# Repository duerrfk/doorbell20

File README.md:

# What is DoorBell20?

Door Bell 2.0 (or DoorBell20 for short) is a Bluetooth Low Energy (BLE) appliance to monitor a door bell and send notifications whenever the door bell rings. It turns a conventional door bell into a smart door bell that can be connected to the Internet of Things (IoT). Thus, DoorBell20 is the modern version of a door bell, or, as the name suggests, the door bell version 2.0 for the IoT era.

DoorBell20 consists for two major parts:

* The DoorBell20 monitoring device, which is connected in parallel to the door bell and wirelessly via BLE to a client running on a remote IoT gateway, e.g., a Raspberry Pi with Bluetooth stick.
* A DoorBell20 client running on the IoT gateway passing on notifications received via BLE to a remote cloud service. Different clients can be implemented for different IoT cloud services. So far, DoorBell20 includes a client for [If This Then That (IFTTT)](https://ifttt.com), which makes it very easy to trigger different actions when a door bell event is detected. For instance, a notification can be sent to a mobile phone or trigger an IP camera installed at the door to take pictures.

```
                  [IoT Cloud Service]
                  [  (e.g., IFTTT)  ]
                           | ^
                 Internet  | | Door Bell Event Notifications
                           |
                [      IoT Gateway      ]
                [ w/ DoorBell20 Client  ]
                [ (e.g., IFTTT Trigger) ]
                           |  ^
           BLE Connection  |  | Door Bell Event Notifications  
                           |
|-----------[DoorBell20 Monitoring Device]---------|
|                                                  |
|--------------------[Door Bell]-------------------|
|                                                  |
|                                                  |
|                                                 \   Door Bell Push Button
|                                                  \
|                                                  |
|----------------(Voltage Source)------------------|
                 (    12 VAC    )
```  

The following images show the DoorBell20 monitoring device, its connection to a door bell, and a door bell event notification displayed by the If This Then That (IFTTT) app on a mobile phone. 

The main features of DoorBell20 are:

* Open-source software and hardware. Source code for the door bell monitoring device and IFTTT client as well as Eagle files (schematic and board layout) are provided.
* Maker-friendly: using easily available cheap standard components (nRF51822 BLE chip, standard electronic parts), easy to manufacture circuit board, and open-source software and hardware design.
* Includes a client for the popular and versatile If This Then That (IFTTT) service to facilitate the development of IoT applications integrating DoorBell20. 
* Liberal licensing of software and hardware under the Apache License 2.0 and the CERN Open Hardware License 1.0, respectively.

# DoorBell20 Monitoring Device

## Hardware

The following images show the DoorBell20 hardware and schematic.

The DoorBell20 monitoring device is based on the BLE chip [nRF51822](https://www.nordicsemi.com/eng/Products/Bluetooth-low-energy/nRF51822) by Nordic Semiconductors. The nRF51822 features an ARM Cortex M0 processor implementing both, the application logic and the BLE stack (so-called softdevice). DoorBell20 uses the S110 softdevice version 8.0. See next sub-section on how to flash the softdevice and the application code. We use a so-called "Bluetooth 4.0" breakout boards with an nRF51822 (version 3, variant AA w/ 16 kB of RAM and 256 kB flash memory) and two 2x9 connectors (2 mm pitch), which you can buy over the Internet for about 6 US$ including shipping.

We isolate the 12 VAC door bell circuit from the microcontroller using an opto-isolator. A rectifier and 5 V voltage regulater is used to power the LED of the opto-isolator whenever the door bell is ringing. A GPIO pin of the nRF51822 connected to the other side of the opto-isolator is then detecting the event. In addition to the integrate protection mechanisms of the LM2940 voltage regulator (short circuit and thermal overload protection, shutdown during transients), a varistor protects from voltage transients since many door bells are inductive loads inducing voltage spikes when switched off. Since varistors age with every voltage transient, a fuse is added to protect the door bell circuit from a short circuit of the varistor.

The nRF51822 is powered by two AA batteries. No additional voltage regulator is required, which increased the energy efficiency, and the monitoring device is expected to run for years from a pair of AA batteries. Note that we did not implement a reverse polarity protection, so be careful to insert the batteries correctly.    

The circuit board layout (PCB) of the DoorBell20 monitoring device for Eagle can be found in folder ```pcb/doorbell20```. We deliberately used a simple single-sided through-hole design to help makers producing their own boards.

## Software/Firmware

The software for the DoorBell20 monitoring device can be found in directory ```nrf51/doorbell20```. 

### Prerequisites for Building the Software

No heavy-weight IDE is required to build the code. However, still a few tools are required to build and flash the code (tested with the given version numbers):

* [nRF51 SDK, version 10.0.0](http://developer.nordicsemi.com/nRF5_SDK/)
* [nRF5x Command Line Tools, version 8.2.0](https://www.nordicsemi.com/eng/Products/nRF51-DK)
* [Softdevice S110, version 8.0.0](https://www.nordicsemi.com/eng/Products/nRF51-DK)
* Flashing and debugging hardware, e.g., [Segger J-Link EDU](https://www.segger.com/j-link-edu.html) (about 50 US$, only for non-commerical use!). The nRF51 Developers Kit (DK) comes with an on-board Segger programmer, but for flashing the DoorBell20 board, you need an external programmer like the J-Link EDU. 
* [Tool chain (compiler, linker, etc.) for ARM](https://launchpad.net/gcc-arm-embedded/+download)

### Building and Flashing the Software

First, adapt the Makefile by defining the following variables:

* `NRF51_SDK`: path to the nRF51 SDK directory
* `CROSS`: path to the compiler tools
* `CFLAGS`: add `-DTARGET_BOARD_NRF51DK` if you compile for the nRF51 Development Kit (DK); if this definition is not set, you compile for the DoorBell20 board.
* `LINKER_SCRIPT`: set to `nrf51422_ac_s110.ld` for the nRF51 DK (nRF51422, variant AC) or to `nrf51822_aa_s110.ld` for the DoorBell20 board (nRF51822, variant AA).

Compiling the code:

```
$ cd nrf51
$ make
```

Flashing the softdevice:

```
$ nrfjprog --family NRF51 --program s110_nrf51_8.0.0_softdevice.hex --chiperase --verify
```

Flashing the application:

```
nrfjprog --family NRF51 --program doorbell20.hex --verify --sectorerase
```

Rebooting after flashing:

```
nrfjprog -r
```

# IFTTT DoorBell20 Client

DoorBell20 can be connected to any BLE client running on a remote machine. After receiveing a BLE notification about a door bell event, the client can then trigger local actions, and can forward the event to a remote IoT cloud service. DoorBell20 comes with a client for connecting to the popular [If This Then That (IFTTT)](https://ifttt.com/) cloud service.

You find the [nodejs](https://nodejs.org/) implementation of the IFTTT client in directory `client/ifttt`. With this client, you can use door bell alarm events as triggers for IFTTT. IFTTT offers you a broad choice of actions such as showing a notification on your smartphone when the bell rings, playing a sound on your phone, or sending a tweet to Twitter (if that makes sense to you). You could also trigger other IoT devices like an IP camera making a picture of the one standing at the door. 

The IFTTT DoorBell20 client subscribes for BLE notifications using the nodejs library [noble](https://github.com/sandeepmistry/noble). Whenever a notification for a door bell alarm is received, a web request is sent to the IFTTT maker channel triggering an event with a pre-defined name (we use the event name `door_bell_alarm` in our example). You can then define your own IFTTT recipes to decide what to do with this event like showing a notification on your smartphone through the IFTTT app. 

The following screenshot shows an IFTTT notification on an Android phone triggered by a door bell event that was delivered over the IFTTT Maker Channel.

## Prerequisites

The IFTTT client relies on the following software to be installed on the BLE client machine (your IoT gateway):

* nodejs (tested with nodejs version 4.6.0)
* noble
* C++ compiler with C++11 support for installing noble with npm as described below (tested with gcc/g++ 4.8.4). If you use Raspbian: gcc/g++ 4.8.4 included with Raspbian Jessie will work, but gcc/g++ 4.6.3 included with Raspbian Wheezy won't.  

Nodejs can be installed as root like this on a Raspberry Pi A/A+, B/B+, and Zero (ARMv6):

```
$ cd /usr/local
$ wget http://nodejs.org/dist/latest-v4.x/node-v4.6.0-linux-armv6l.tar.xz
$ tar axf node-v4.6.0-linux-armv6l.tar.xz
```

For other platforms, you have to replace `node-v4.6.0-linux-armv6l.tar.xz` by the corresponding file, e.g., `node-v4.6.0-linux-armv7l.tar.xz` for Raspberry Pi 2 (ARMv7) or `node-v4.6.0-linux-x64.tar.xz` for 64 bit Linux.

Make sure to add the nodejs `bin` directory to your path, so the commands `node`and `npm` can be found.

With nodejs installed, install the noble library for implementing BLE centrals:

```
$ sudo apt-get install bluetooth bluez libbluetooth-dev libudev-dev
$ cd doorbell20/client/ifttt
$ npm install noble
```

This should create the sub-directory `node_modules` in directory `doorbell20/client/ifttt`.

The first line installs Bluetooth libraries required by noble on Debian-based systems including Ubuntu and Raspbian. You might need to modify this depending on your platform, e.g., for Fedora:

```
$ sudo yum install bluez bluez-libs bluez-libs-devel
```

Please consult the [noble page](https://github.com/sandeepmistry/noble) for other platforms.

## Executing the IFTTT Client

The client can be started like this:

```
sudo node doorbell20-client-ifttt.js 'ABCDEFGHIJK1234567890' 'f3:23:0d:4c:ce:1b' 'doorbell_alarm' 'iot_failure'
```

Argument `ABCDEFGHIJK1234567890` is the key of your IFTTT Maker channel (obviously here a bogus one), which you get when you register with the Maker channel through the IFTTT web interface or app.

Argument `doorbell_alarm` is the name of the generated events. You can send many different events to your Maker channel, e.g., from your door bell, from your smoke detector (hopefully not so often), etc. The event name defines, which event has been fired.

A second event called `iot_failure` is defined that will be triggerer when the client could not connect to the DoorBell20 monitoring device over BLE to signal a permanent failure, e.g., when the battery of the monitoring device is empty. 

Argument `f3:23:0d:4c:ce:1b` is the MAC address of your DoorBell20 BLE device. You might have installed different DoorBell20 devices for different door bells, so the DoorBell20 service UUID is not enough to distinguish between different devices. The MAC address is unique for each device.

## Source Code

The source code of the IFTTT client can be found in file `doorbell20-client-ifttt.js`. It should be pretty self-explaining.

Event notifications are sent to the IFTTT channel through web requests using HTTPS. The URL defines the triggered event:

```
https://maker.ifttt.com/trigger/{event}/with/key/{key}
```

```{event}``` and ```{key}``` are replaced by the above command line arguments to define the event type and Maker channel. 

A POST request is used to send a simple JSON document with this format:

```
{ "value1" : "2016-10-09 18:37:34", "value2" : "", "value3" : "" }
```

In our application, ```value1``` defines the time when the door bell alarm event has been detected. The other two values are unused.

The client subscribes to BLE/GATT notifications of the door bell alarm characteristic of the DoorBell20 service using noble. When a BLE/GATT notification is sent, the client determines the local time of the client machine. Note that the BLE device has no wall clock time available (although is sends the local up-time of the device with every notification and allows for querying the local device time time through another characteristic). The time of the client machine is sent as timestamp of the IFTTT event notification as `value1`.

# License and Acknowledgments

The DoorBell20 software (contents of folders `nrf51` and `client`) is licensed under the Apache License, Version 2.0.

The DoorBell20 hardware documentation (contents of folder `pcb`) is licensed under the CERN Open Hardware Licence, Version 1.2

Both licenses are included in the repository in the files `LICENSE-SOFTWARE` and `LICENSE-HARDWARE`, respectively.

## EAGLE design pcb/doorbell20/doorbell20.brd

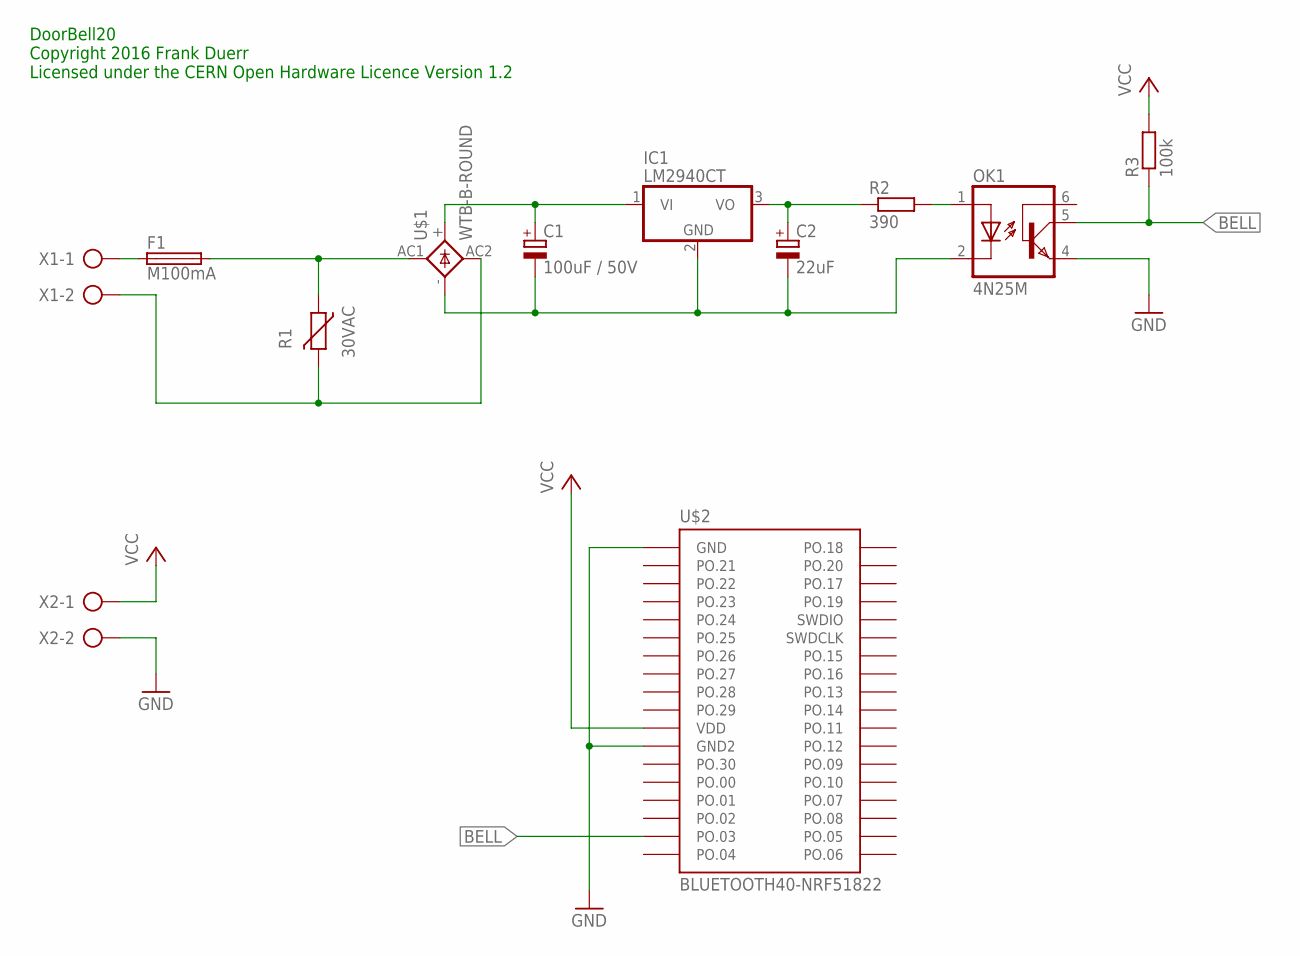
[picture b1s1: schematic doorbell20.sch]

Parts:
C1: 100uF / 50V; E5-10,5
C2: 22uF; E2,5-5
F1: M100mA; SH22,5A
IC1: LM2940CT; TO220V
OK1: 4N25M; DIL06
R1: 30VAC; R-7,5
R2: 390; 0207/7
R3: 100k; 0207/7
U$1: WTB-B-ROUND; WTE-B-ROUND
U$2: BLUETOOTH40-NRF51822; BLUETOOTH40-NR51822
X1, X2: AK500/2

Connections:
BELL: OK1.5 (COL), R3.1, U$2.PO.03
GND: OK1.4 (EMI), U$2.GND, U$2.GND2, X2.2
unnamed: F1.1, X1.1
unnamed: F1.2, R1.1, U$1.AC1
unnamed: C1.-, C2.-, IC1.2 (GND), OK1.2 (C), U$1.-
unnamed: C1.+, IC1.1 (VI), U$1.+
unnamed: OK1.1 (A), R2.2
unnamed: R1.2, U$1.AC2, X1.2
unnamed: C2.+, IC1.3 (VO), R2.1
VCC: R3.2, U$2.VDD, X2.1

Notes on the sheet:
DoorBell20 Copyright 2016 Frank Duerr Licensed under the CERN Open Hardware Licence Version 1.2

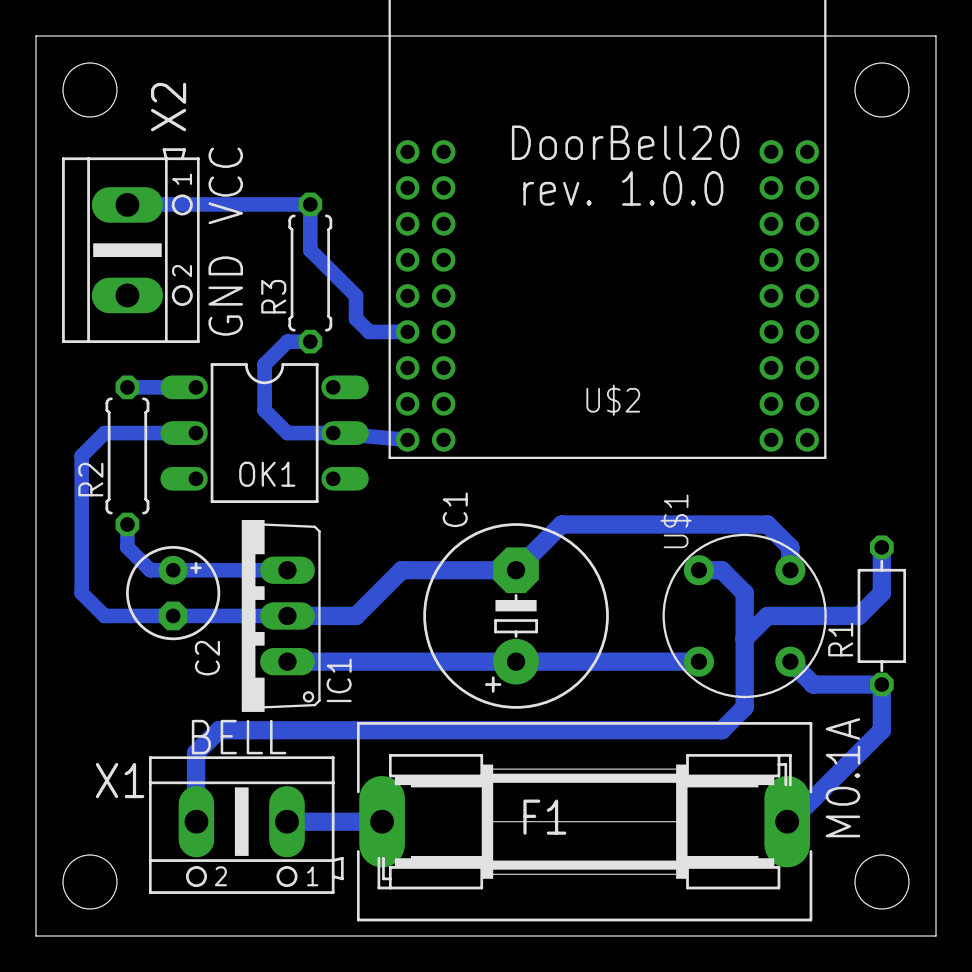
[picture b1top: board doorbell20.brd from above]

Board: 2 copper layers, 50.0 x 50.0 mm, 12 parts (0 on the bottom side), 10 nets.

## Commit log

2016-10-09 Initial check-in
2016-10-09 Added IFTTT client.
2016-10-09 Added readme file.
2016-10-15 Added disconnection timeout to IFTTT client. Rebooting BLE device in case of errors.
2016-10-16 Added failure event notification to IFTTT client.
2016-11-12 Added licenses
2016-11-12 Added information to README
2016-11-12 Added screenshot and schematic image.
2016-11-12 Added images.
2016-11-12 Revised README
